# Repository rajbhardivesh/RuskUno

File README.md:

# RuskUno — Arduino® alternative based on MindMotion MM32F0141C6P

**RuskUno** is an open-source development board designed as an Arduino-style alternative built around the MindMotion **MM32F0141C6P** (ARM Cortex-M0).  
This repo contains the KiCad hardware sources and initial documentation. An Arduino-style core / cores for this MCU is **in progress** and will be provided here when ready.

This repository contains:

- ✅ Full KiCad hardware source files
- 🚧 Arduino-compatible core (In Progress)
- 🔓 Open Source Hardware

---

# 📸 Development Board

## Top View

## Bottom View

---

# 🧠 Why RuskUno?

The goal of RuskUno is to provide:

- Higher performance than ATmega328P
- More Flash & RAM
- Modern 32-bit ARM architecture
- Open hardware design
- Future Arduino ecosystem compatibility
- Affordable alternative for students & developers

---

# ⚙️ Microcontroller Overview

## 🔹 MM32F0141C6P

- Core: ARM Cortex-M0 (32-bit)
- Max Clock: 72 MHz
- Flash: 64 KB
- SRAM: 8 KB
- Multiple UART / SPI / I2C
- 12-bit ADC
- Advanced Timers
- SWD Debug Support

---

# 🔄 Comparison: MM32F0141C6P vs ATmega328P

| Feature | MM32F0141C6P | ATmega328P |
|----------|---------------|--------------|
| Architecture | 32-bit ARM Cortex-M0 | 8-bit AVR |
| Max Frequency | 72 MHz | 20 MHz |
| Flash | 64 KB | 32 KB |
| SRAM | 8 KB | 2 KB |
| ADC | 12-bit | 10-bit |
| Debug | SWD | No native debugger |
| Performance | High | Moderate |
| Math Speed | Fast 32-bit | Slower 8-bit |

**Result:**  
RuskUno offers significantly better performance, memory headroom, and peripheral flexibility compared to traditional Arduino UNO.

---

# 🛠 Hardware Features

- Arduino-style pin header layout
- USB programming interface
- External crystal
- SWD debug header
- 3.3V logic
- Power via USB or VIN
- LDO regulator onboard
- Status LED
- Reset button

---

# 🧩 Arduino Core (In Progress)

The Arduino-compatible core is currently under development.

Planned features:
- Arduino pin mapping
- digitalWrite / digitalRead
- analogRead
- PWM
- Serial support
- SPI & I2C
- Timer support

Once stable, the core will be:
- Added in `/firmware`
- Packaged for Arduino IDE board manager

Stay tuned ⭐

---

# 🎯 Project Vision

RuskUno aims to:

- Provide a powerful yet affordable board for students
- Enable migration from 8-bit AVR to 32-bit ARM easily
- Offer fully open hardware
- Support embedded learners
- Build an ecosystem around MM32 microcontrollers

---

# 🤝 Contributing

Pull requests are welcome!

If you'd like to contribute:
1. Fork the repository
2. Create a feature branch
3. Commit your changes
4. Submit a PR

---

# 📌 Roadmap

- [x] Hardware Design Complete
- [x] Prototype Built
- [ ] Arduino Core Development
- [ ] Bootloader
- [ ] Documentation Expansion
- [ ] Example Projects

---

# 🌍 Open Hardware Commitment

RuskUno is 100% open-source.

KiCad files are provided.
Anyone can:
- Study
- Modify
- Manufacture
- Improve

---

# 👨‍💻 Author

Designed & Developed by  
**Rajbhar Divesh**

---

# 🔓 License

This project is licensed under the MIT License.

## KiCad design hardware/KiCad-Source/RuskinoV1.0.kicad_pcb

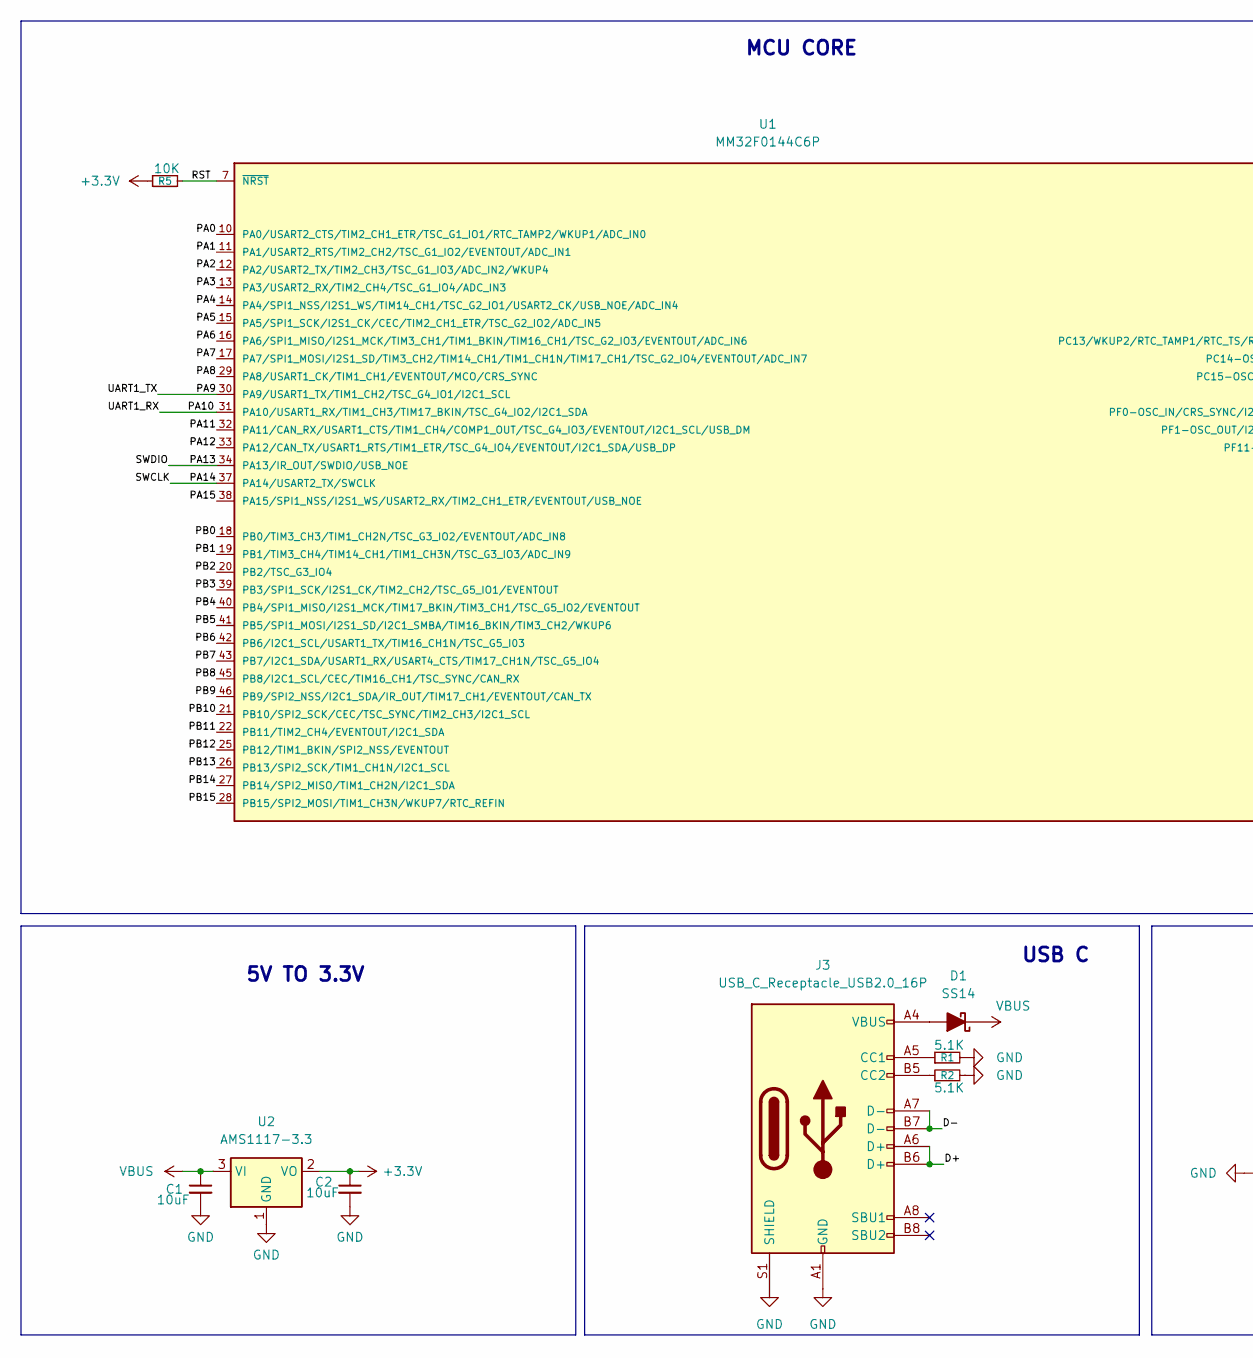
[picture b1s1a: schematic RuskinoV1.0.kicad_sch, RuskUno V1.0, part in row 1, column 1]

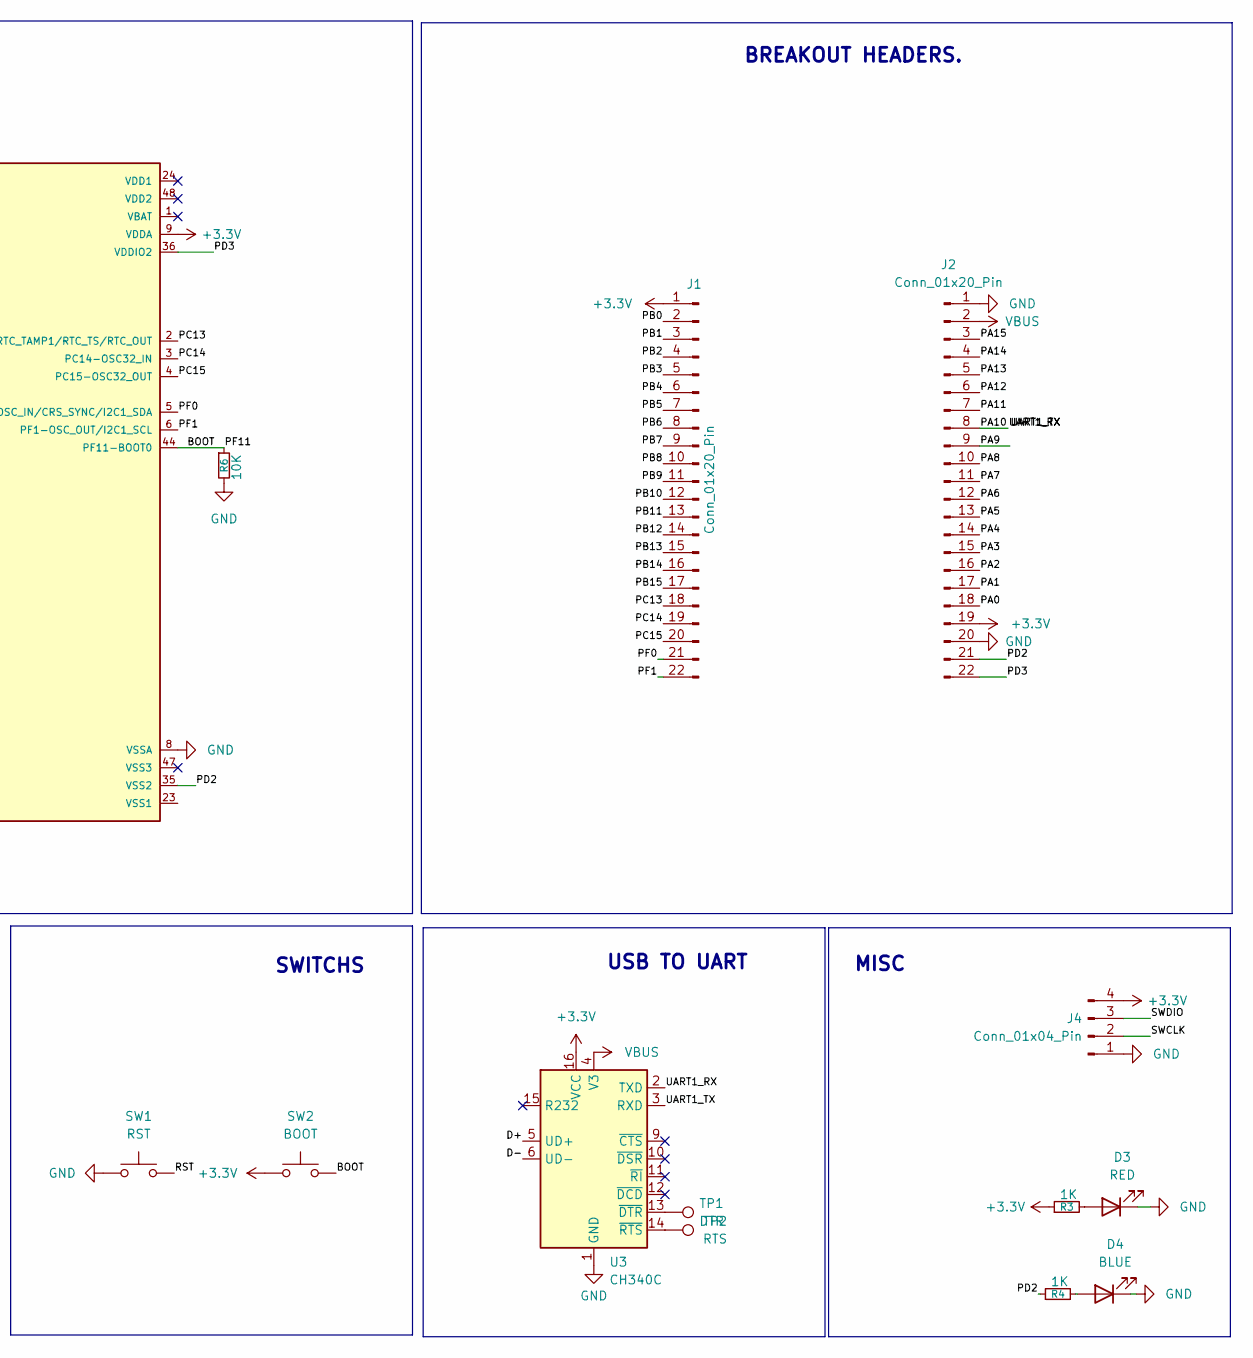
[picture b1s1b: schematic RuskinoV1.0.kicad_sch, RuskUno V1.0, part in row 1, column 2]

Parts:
C1, C2: 10uF; C_1206_3216Metric_Pad1.33x1.80mm_HandSolder
D1: SS14; D_SOD-123
D3: RED; LED_0603_1608Metric_Pad1.05x0.95mm_HandSolder
D4: BLUE; LED_0603_1608Metric_Pad1.05x0.95mm_HandSolder
J1, J2: Conn_01x20_Pin; PinHeader_1x22_P2.54mm_Vertical
J3: USB_C_Receptacle_USB2.0_16P; USB_C_Receptacle_GCT_USB4105-xx-A_16P_TopMnt_Horizontal
J4: Conn_01x04_Pin; PinHeader_1x04_P2.54mm_Horizontal
R1, R2: 5.1K; R_0805_2012Metric_Pad1.15x1.40mm_HandSolder
R3, R4: 1K; R_0805_2012Metric_Pad1.15x1.40mm_HandSolder
R5, R6: 10K; R_0805_2012Metric_Pad1.15x1.40mm_HandSolder
SW1: RST; SW_SPST_TS-1088-xR020
SW2: BOOT; SW_SPST_TS-1088-xR020
TP1: DTR; TestPoint_Pad_D1.0mm
TP2: RTS; TestPoint_Pad_D1.0mm
U1: MM32F0144C6P; QFP50P700X700X160-48N
U2: AMS1117-3.3; SOT-223-3_TabPin2
U3: CH340C; SOIC-16_3.9x9.9mm_P1.27mm

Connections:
+3.3V: C2.1, J1.1, J2.19, J4.4, R3.1, R5.1, SW2.1, U1.9 (VDDA), U2.2 (VO), U3.16 (VCC)
/BOOT: R6.1, SW2.2, U1.44 (PF11-BOOT0)
/D+: J3.A6 (D+), J3.B6 (D+), U3.5 (UD+)
/D-: J3.A7 (D-), J3.B7 (D-), U3.6 (UD-)
/PA0: J2.18, U1.10 (PA0/USART2_CTS/TIM2_CH1_ETR/TSC_G1_IO1/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)
/PA1: J2.17, U1.11 (PA1/USART2_RTS/TIM2_CH2/TSC_G1_IO2/EVEN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)
/PA2: J2.16, U1.12 (PA2/USART2_TX/TIM2_CH3/TSC_G1_IO3/ADC_I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)
/PA3: J2.15, U1.13 (PA3/USART2_RX/TIM2_CH4/TSC_G1_IO4/ADC_I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)
/PA4: J2.14, U1.14 (PA4/SPI1_NSS/I2S1_WS/TIM14_CH1/TSC_G2_I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)
/PA5: J2.13, U1.15 (PA5/SPI1_SCK/I2S1_CK/CEC/TIM2_CH1_ETR/T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)
/PA6: J2.12, U1.16 (PA6/SPI1_MISO/I2S1_MCK/TIM3_CH1/TIM1_BK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)
/PA7: J2.11, U1.17 (PA7/SPI1_MOSI/I2S1_SD/TIM3_CH2/TIM14_CH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)
/PA8: J2.10, U1.29 (PA8/USART1_CK/TIM1_CH1/EVENTOUT/MCO/CRS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)
/PA9: J2.9, U1.30 (PA9/USART1_TX/TIM1_CH2/TSC_G4_IO1/I2C1_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), U3.3 (RXD)
/PA10: J2.8, U1.31 (PA10/USART1_RX/TIM1_CH3/TIM17_BKIN/TSC_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), U3.2 (TXD)
/PA11: J2.7, U1.32 (PA11/CAN_RX/USART1_CTS/TIM1_CH4/COMP1_O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)
/PA12: J2.6, U1.33 (PA12/CAN_TX/USART1_RTS/TIM1_ETR/TSC_G4_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)
/PA13: J2.5, J4.3, U1.34 (PA13/IR_OUT/SWDIO/USB_NOE)
/PA14: J2.4, J4.2, U1.37 (PA14/USART2_TX/SWCLK)
/PA15: J2.3, U1.38 (PA15/SPI1_NSS/I2S1_WS/USART2_RX/TIM2_CH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)
/PB0: J1.2, U1.18 (PB0/TIM3_CH3/TIM1_CH2N/TSC_G3_IO2/EVENT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)
/PB1: J1.3, U1.19 (PB1/TIM3_CH4/TIM14_CH1/TIM1_CH3N/TSC_G3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)
/PB2: J1.4, U1.20 (PB2/TSC_G3_IO4)
/PB3: J1.5, U1.39 (PB3/SPI1_SCK/I2S1_CK/TIM2_CH2/TSC_G5_IO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)
/PB4: J1.6, U1.40 (PB4/SPI1_MISO/I2S1_MCK/TIM17_BKIN/TIM3_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)
/PB5: J1.7, U1.41 (PB5/SPI1_MOSI/I2S1_SD/I2C1_SMBA/TIM16_B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)
/PB6: J1.8, U1.42 (PB6/I2C1_SCL/USART1_TX/TIM16_CH1N/TSC_G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)
/PB7: J1.9, U1.43 (PB7/I2C1_SDA/USART1_RX/USART4_CTS/TIM17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)
/PB8: J1.10, U1.45 (PB8/I2C1_SCL/CEC/TIM16_CH1/TSC_SYNC/CAN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)
/PB9: J1.11, U1.46 (PB9/SPI2_NSS/I2C1_SDA/IR_OUT/TIM17_CH1/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)
/PB10: J1.12, U1.21 (PB10/SPI2_SCK/CEC/TSC_SYNC/TIM2_CH3/I2C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)
/PB11: J1.13, U1.22 (PB11/TIM2_CH4/EVENTOUT/I2C1_SDA)
/PB12: J1.14, U1.25 (PB12/TIM1_BKIN/SPI2_NSS/EVENTOUT)
/PB13: J1.15, U1.26 (PB13/SPI2_SCK/TIM1_CH1N/I2C1_SCL)
/PB14: J1.16, U1.27 (PB14/SPI2_MISO/TIM1_CH2N/I2C1_SDA)
/PB15: J1.17, U1.28 (PB15/SPI2_MOSI/TIM1_CH3N/WKUP7/RTC_REFIN)
/PC13: J1.18, U1.2 (PC13/WKUP2/RTC_TAMP1/RTC_TS/RTC_OUT)
/PC14: J1.19, U1.3 (PC14-OSC32_IN)
/PC15: J1.20, U1.4 (PC15-OSC32_OUT)
/PD2: J2.21, R4.1, U1.35 (VSS2)
/PD3: J2.22, U1.36 (VDDIO2)
/PF0: J1.21, U1.5 (PF0-OSC_IN/CRS_SYNC/I2C1_SDA)
/PF1: J1.22, U1.6 (PF1-OSC_OUT/I2C1_SCL)
/RST: R5.2, SW1.2, U1.7 (~NRST)
GND: C1.2, C2.2, D3.1 (K), D4.1 (K), J2.1, J2.20, J3.A1 (GND), J3.A12 (GND), J3.B1 (GND), J3.B12 (GND), J3.S1 (SHIELD), J4.1, R1.2, R2.2, R6.2, SW1.1, U1.8 (VSSA), U2.1 (GND), U3.1 (GND)
unnamed: D1.2 (A), J3.A4 (VBUS), J3.A9 (VBUS), J3.B4 (VBUS), J3.B9 (VBUS)
unnamed: D3.2 (A), R3.2
unnamed: D4.2 (A), R4.2
unnamed: J3.A5 (CC1), R1.1
unnamed: J3.B5 (CC2), R2.1
unnamed: TP1.1, U3.13 (~DTR)
unnamed: TP2.1, U3.14 (~RTS)
VBUS: C1.1, D1.1 (K), J2.2, U2.3 (VI), U3.4 (V3)

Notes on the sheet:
MISC
USB TO UART
5V TO 3.3V
BREAKOUT HEADERS.
MCU CORE
USB C
SWITCHS

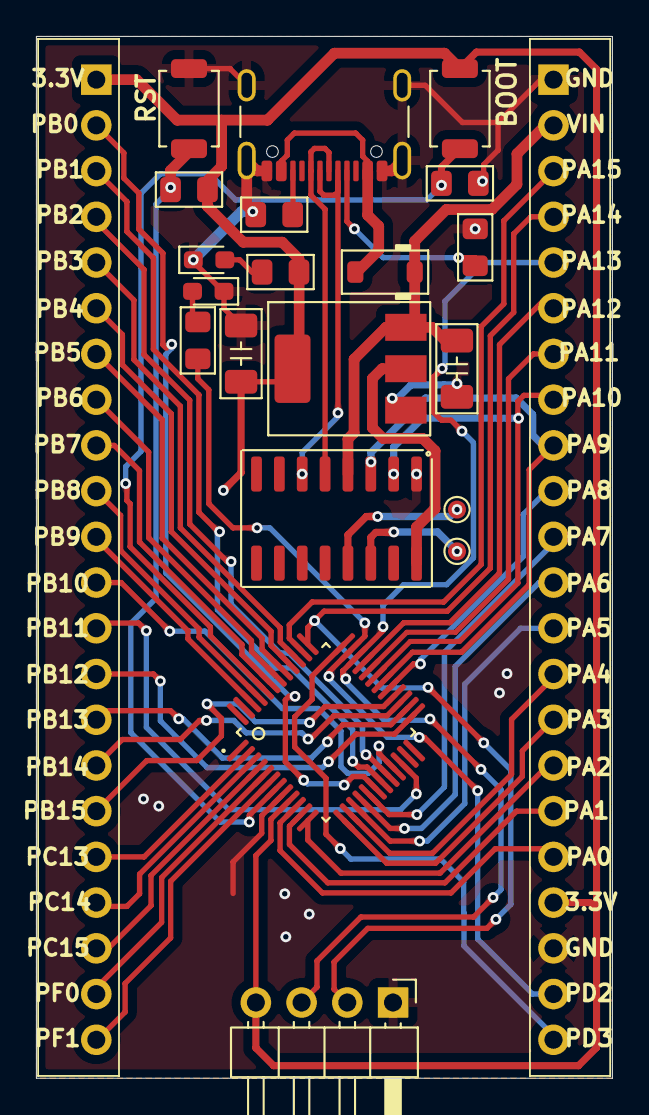
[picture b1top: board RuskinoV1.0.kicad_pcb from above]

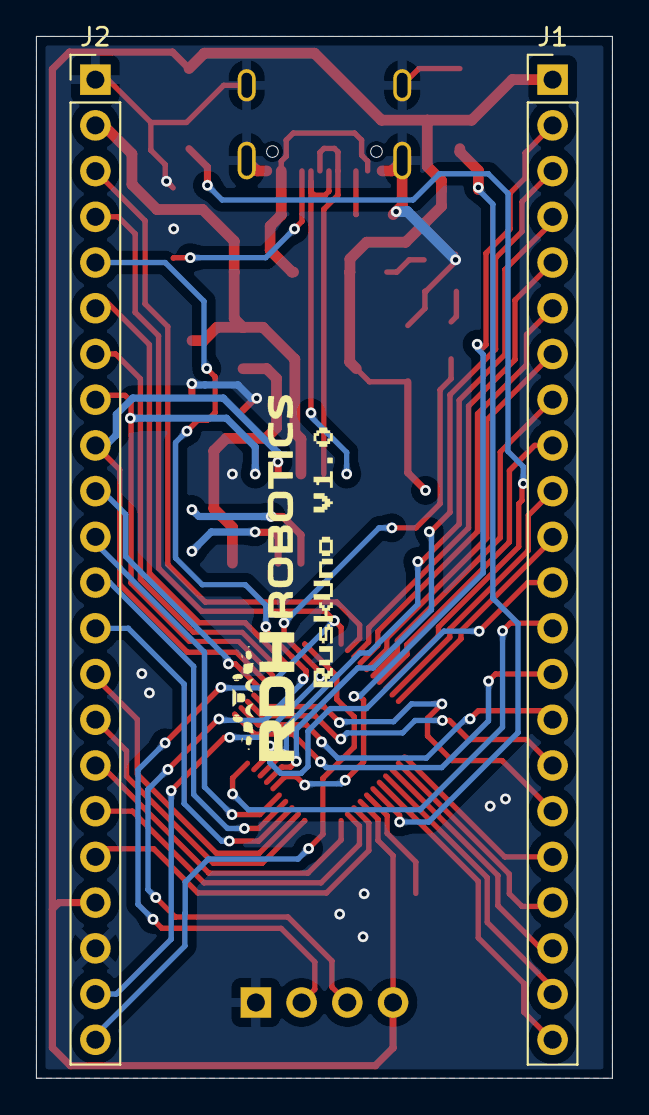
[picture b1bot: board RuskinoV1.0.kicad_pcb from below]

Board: 2 copper layers, 32.0 x 57.9 mm, 22 parts (2 on the bottom side), 53 nets.

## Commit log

2026-03-03 Revise README for RuskUno project details
    Updated README to enhance clarity and detail about RuskUno.
2026-03-03 Initial Upload
2026-03-03 Fix image paths in README.md
    Corrected image path casing for consistency.
